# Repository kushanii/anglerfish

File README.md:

# anglerfish
Anglerfish PCB Art

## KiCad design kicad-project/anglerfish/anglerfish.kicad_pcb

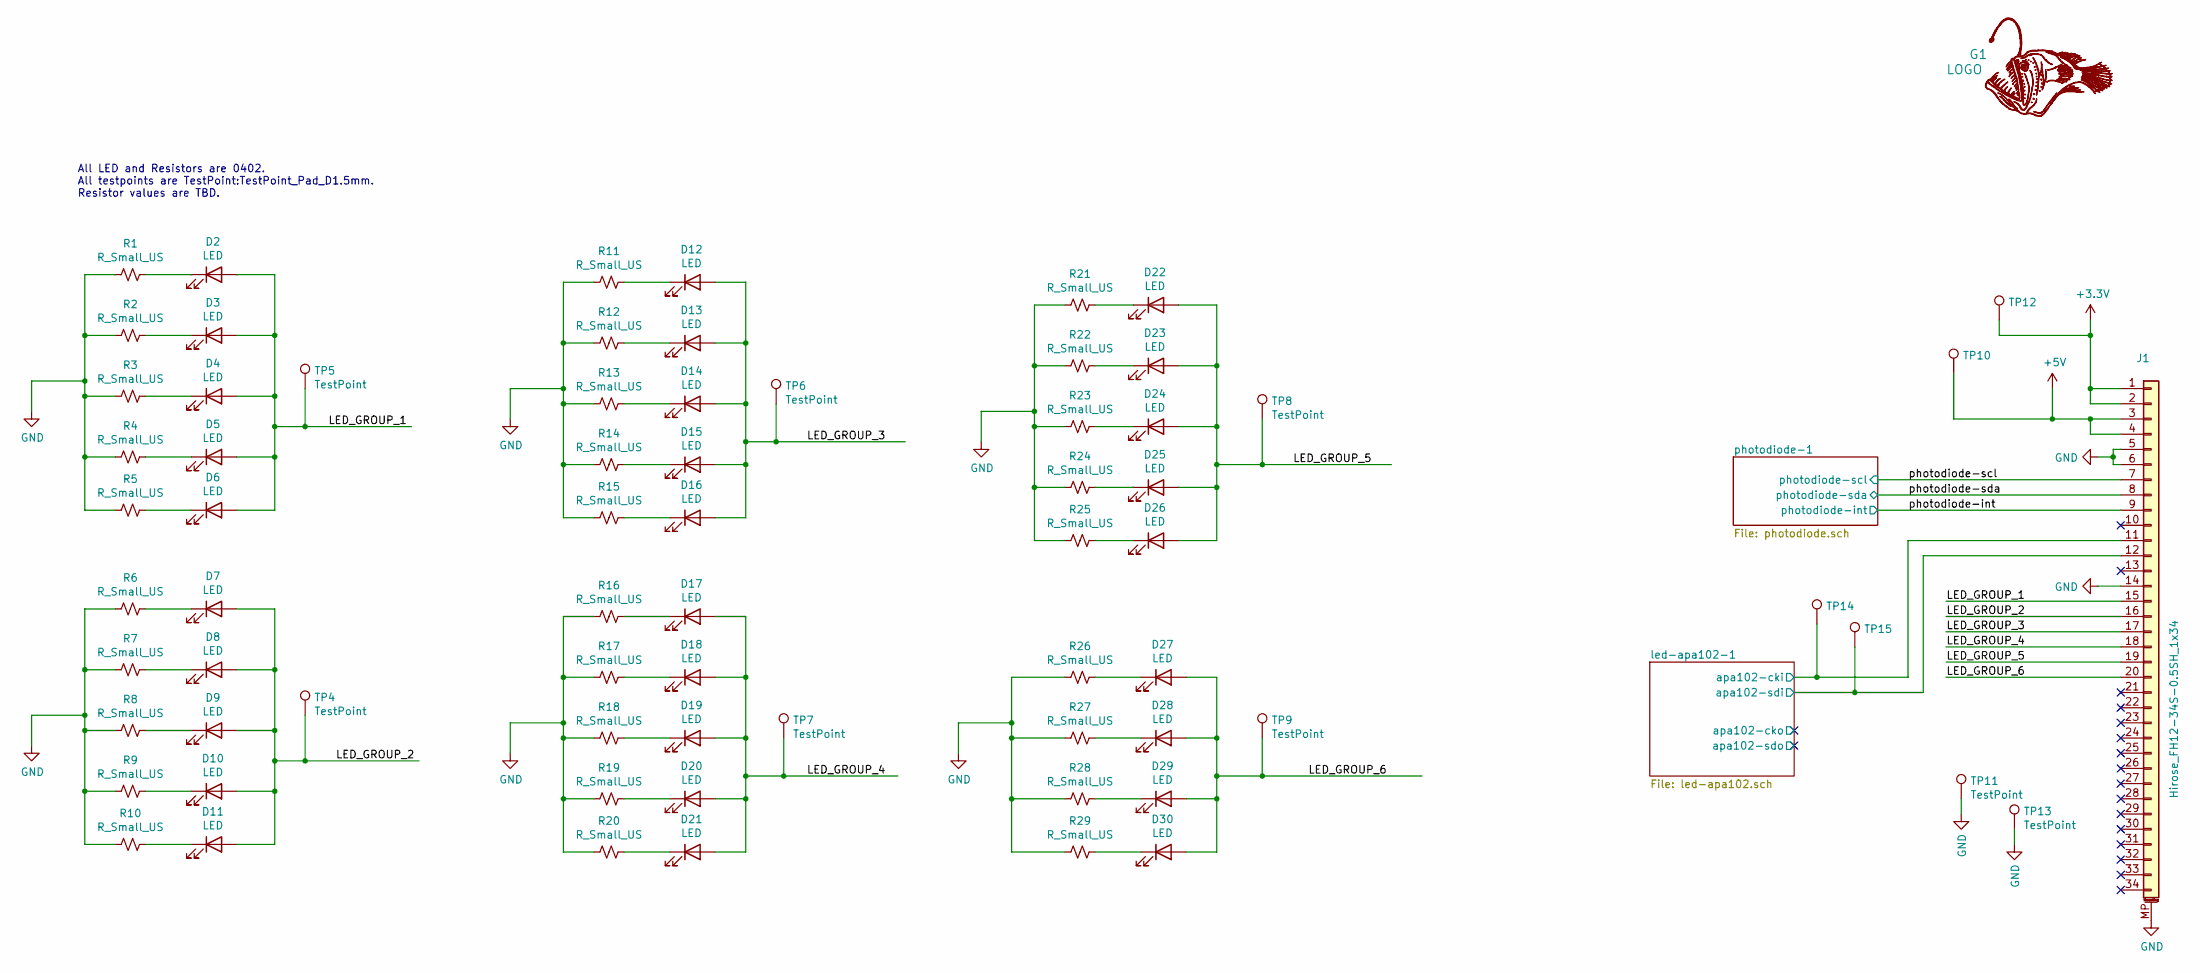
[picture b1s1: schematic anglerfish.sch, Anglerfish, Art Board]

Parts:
D2, D3, D4, D5, D6, D7, D8, D9, D10, D11, D12, D13, D14, D15, D16, D17, D18, D19, D20, D21, D22, D23, D24, D25, D26, D27, D28, D29, D30: LED; LED_0402_1005Metric; LCSC Part C130725
G1: LOGO; anglerfish
J1: Hirose_FH12-34S-0.5SH_1x34; Hirose_FH12-34S-0.5SH_1x34-1MP_P0.50mm_Horizontal
R1, R2, R3, R4, R5, R6, R7, R8, R9, R10, R11, R12, R13, R14, R15, R16, R17, R18, R19, R20, R21, R22, R23, R24, R25, R26, R27, R28, R29: R_Small_US; R_0402_1005Metric
TP4, TP5, TP6, TP7, TP8, TP9, TP10, TP11, TP12, TP13, TP14, TP15: TestPoint; TestPoint_Pad_D1.5mm

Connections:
+3V3: J1.1, J1.2, TP12.1; also elsewhere on the board
+5V: J1.3, J1.4, TP10.1; also elsewhere on the board
/LED_GROUP_1: D2.2 (A), D3.2 (A), D4.2 (A), D5.2 (A), D6.2 (A), J1.15, TP5.1
/LED_GROUP_2: D7.2 (A), D8.2 (A), D9.2 (A), D10.2 (A), D11.2 (A), J1.16, TP4.1
/LED_GROUP_3: D12.2 (A), D13.2 (A), D14.2 (A), D15.2 (A), D16.2 (A), J1.17, TP6.1
/LED_GROUP_4: D17.2 (A), D18.2 (A), D19.2 (A), D20.2 (A), D21.2 (A), J1.18, TP7.1
/LED_GROUP_5: D22.2 (A), D23.2 (A), D24.2 (A), D25.2 (A), D26.2 (A), J1.19, TP8.1
/LED_GROUP_6: D27.2 (A), D28.2 (A), D29.2 (A), D30.2 (A), J1.20, TP9.1
/led-apa102-1/apa102-cki: J1.11, TP14.1; also elsewhere on the board
/led-apa102-1/apa102-sdi: J1.12, TP15.1; also elsewhere on the board
/photodiode-int: J1.9; also elsewhere on the board
/photodiode-scl: J1.7; also elsewhere on the board
/photodiode-sda: J1.8; also elsewhere on the board
GND: J1.5, J1.6, J1.14, J1.MP (MountPin), R1.2, R2.2, R3.2, R4.2, R5.2, R6.2, R7.2, R8.2, R9.2, R10.2, R11.2, R12.2, R13.2, R14.2, R15.2, R16.2, R17.2, R18.2, R19.2, R20.2, R21.2, R22.2, R23.2, R24.2, R25.2, R26.2, R27.2, R28.2, R29.2, TP11.1, TP13.1; also elsewhere on the board
unnamed: D2.1 (K), R1.1
unnamed: D3.1 (K), R2.1
unnamed: D4.1 (K), R3.1
unnamed: D5.1 (K), R4.1
unnamed: D6.1 (K), R5.1
unnamed: D7.1 (K), R6.1
unnamed: D8.1 (K), R7.1
unnamed: D9.1 (K), R8.1
unnamed: D10.1 (K), R9.1
unnamed: D11.1 (K), R10.1
unnamed: D12.1 (K), R11.1
unnamed: D13.1 (K), R12.1
unnamed: D14.1 (K), R13.1
unnamed: D15.1 (K), R14.1
unnamed: D16.1 (K), R15.1
unnamed: D17.1 (K), R16.1
unnamed: D18.1 (K), R17.1
unnamed: D19.1 (K), R18.1
unnamed: D20.1 (K), R19.1
unnamed: D21.1 (K), R20.1
unnamed: D22.1 (K), R21.1
unnamed: D23.1 (K), R22.1
unnamed: D24.1 (K), R23.1
unnamed: D25.1 (K), R24.1
unnamed: D26.1 (K), R25.1
unnamed: D27.1 (K), R26.1
unnamed: D28.1 (K), R27.1
unnamed: D29.1 (K), R28.1
unnamed: D30.1 (K), R29.1

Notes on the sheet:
All LED and Resistors are 0402. All testpoints are TestPoint:TestPoint_Pad_D1.5mm. Resistor values are TBD.

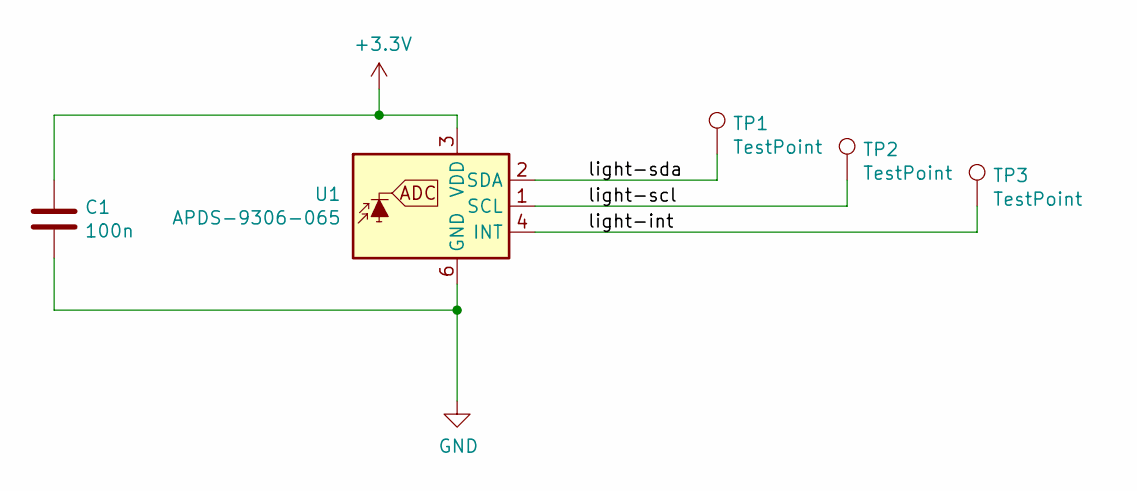
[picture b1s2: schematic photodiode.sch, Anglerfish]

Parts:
C1: 100n; C_0402_1005Metric
TP1, TP2, TP3: TestPoint; TestPoint_Pad_D1.5mm
U1: APDS-9306-065; Broadcom_DFN-6_2x2mm_P0.65mm

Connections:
+3V3: C1.1, U1.3 (VDD); also elsewhere on the board
/photodiode-int: TP3.1, U1.4 (INT); also elsewhere on the board
/photodiode-scl: TP2.1, U1.1 (SCL); also elsewhere on the board
/photodiode-sda: TP1.1, U1.2 (SDA); also elsewhere on the board
GND: C1.2, U1.6 (GND); also elsewhere on the board

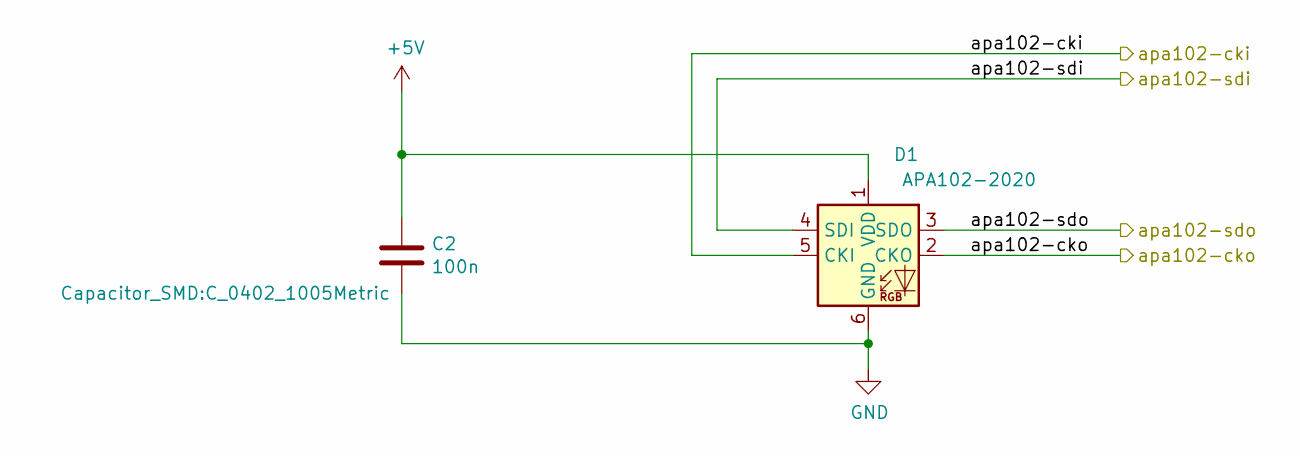
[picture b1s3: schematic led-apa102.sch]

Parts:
C2: 100n; C_0402_1005Metric
D1: APA102-2020; LED-APA102-2020

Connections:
+5V: C2.1, D1.1 (VDD); also elsewhere on the board
/led-apa102-1/apa102-cki: D1.5 (CKI); also elsewhere on the board
/led-apa102-1/apa102-cko: D1.2 (CKO)
/led-apa102-1/apa102-sdi: D1.4 (SDI); also elsewhere on the board
/led-apa102-1/apa102-sdo: D1.3 (SDO)
GND: C2.2, D1.6 (GND); also elsewhere on the board

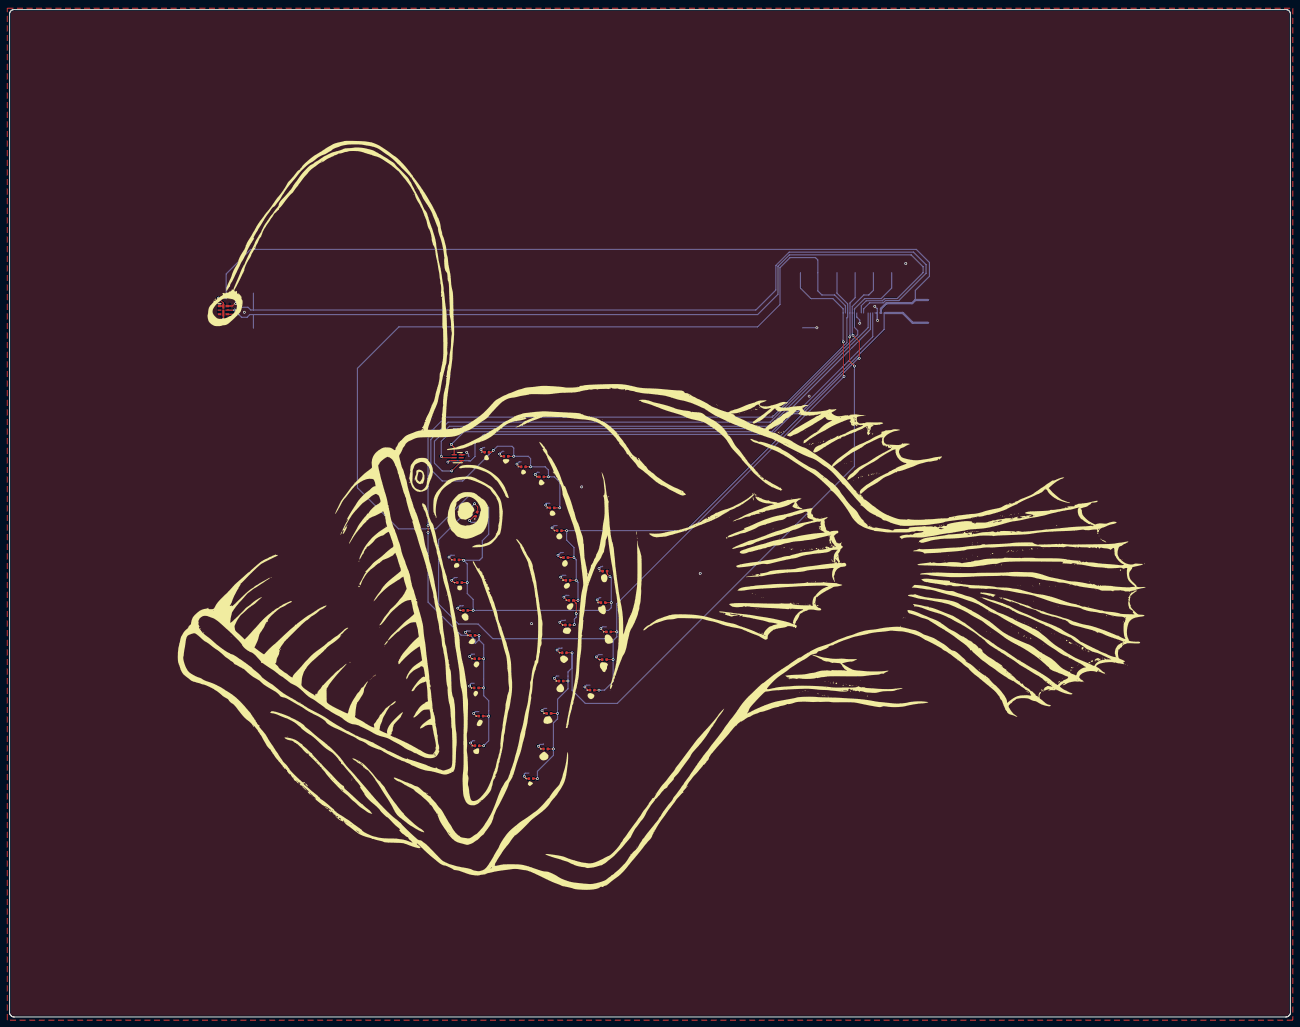
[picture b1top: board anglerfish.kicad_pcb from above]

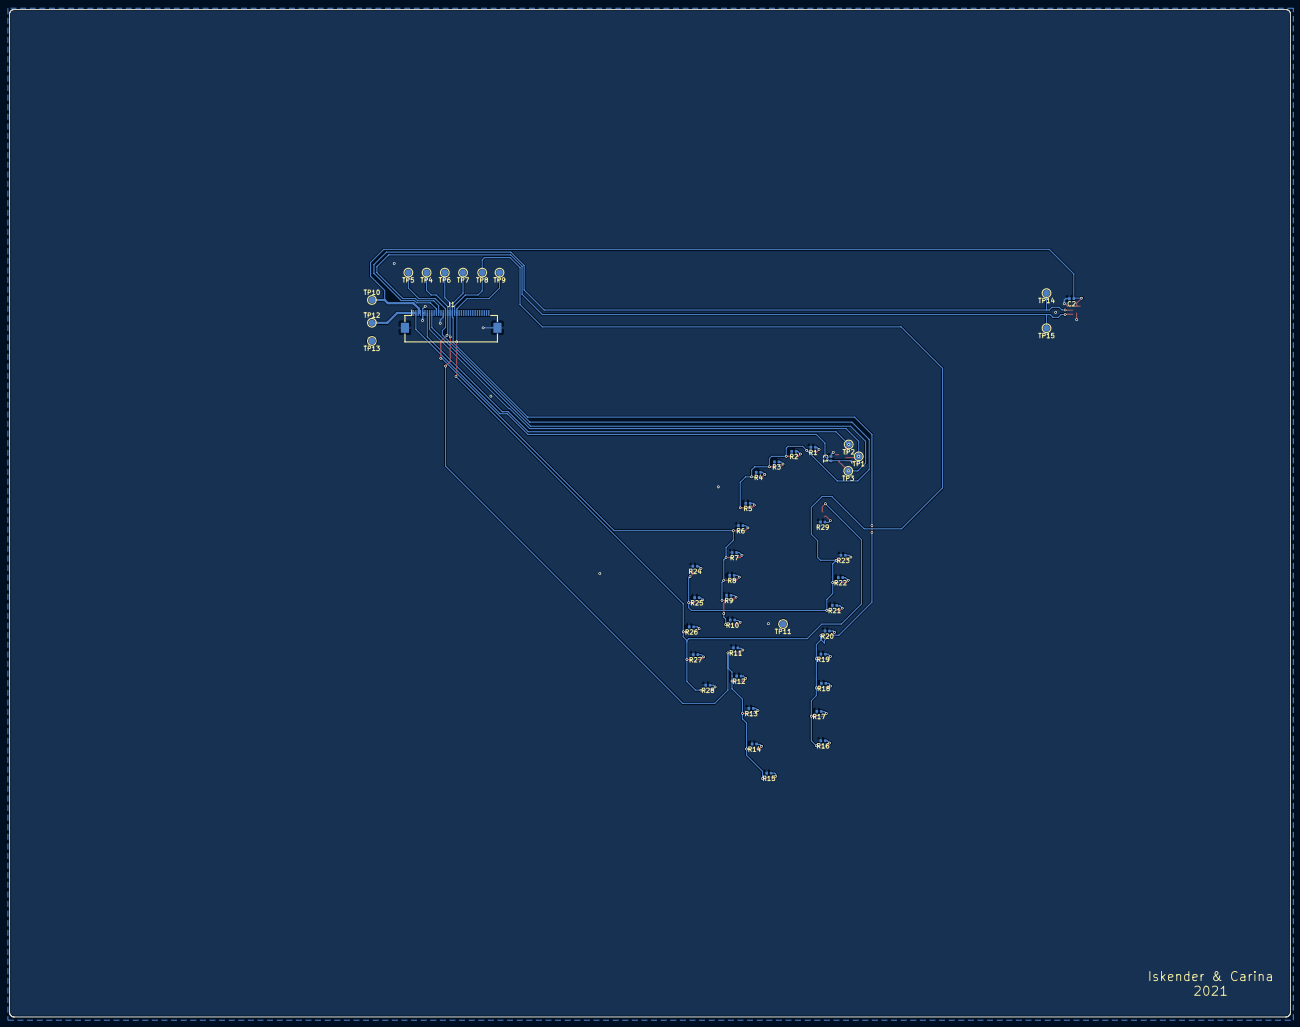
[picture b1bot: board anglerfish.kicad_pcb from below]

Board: 2 copper layers, 281.0 x 221.0 mm, 79 parts (47 on the bottom side), 43 nets.

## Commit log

2020-12-26 Adding the fish images + first commit of the KiCad Project.
2020-12-27 Added the 0402 whites. Also added the APA.
2020-12-27 Added the photodiode.
2020-12-27 Created a placeholder FW folder.
2020-12-28 Started the driver project. Thinking of doing a BQ240x charger.
2021-01-25 ZIF connector added.
2021-01-31 Schematic entered. Adding placing the resistors in the layout now.
2021-02-10 Did placement. Need to edit the silkscreen layer to carve out an opening for the neo LED.
2021-02-18 Routed the LED's and their resistors. Placed comments on the areas where the artwork needs rework.
2021-02-22 Finished routing. trying to generate a bom.
2021-02-22 Generated a pick and place file. Made jlcsmt files for fabrication (bom and .cmp)
2021-03-05 I think it is done! Going to do a review tomorrow and make sure the BOM and PNP are good to go too.
2021-03-06 Generated gerbers. I discovered that I was working in a temp folder, so I erased the files under the anglerfish folder and manually brought the files from the temp folder.
